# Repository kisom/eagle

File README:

Various EagleCAD projects.

Unless specified otherwise in the schematic frame, all projects are
released under the CC-BY-SA 3.0 license.

Links:
	SFE Eagle parts library: https://github.com/sparkfun/SparkFun-Eagle-Libraries.git
	CC-BY-SA 3.0: http://creativecommons.org/licenses/by-sa/3.0

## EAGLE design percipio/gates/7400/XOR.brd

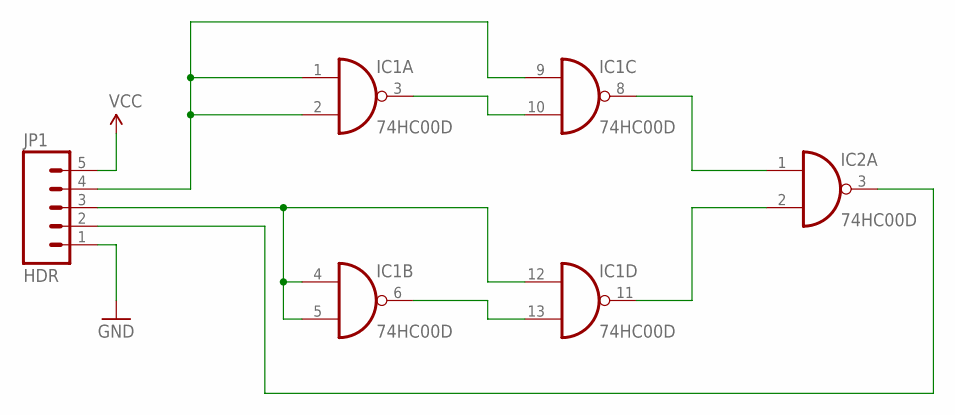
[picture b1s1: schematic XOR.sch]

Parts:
IC1, IC2: 74HC00D; SO14
JP1: HDR; 1X05_LOCK

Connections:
GND: IC1.7 (GND), IC2.7 (GND), JP1.1
unnamed: IC1.1 (I0), IC1.2 (I1), IC1.9 (I0), JP1.4
unnamed: IC1.3 (O), IC1.10 (I1)
unnamed: IC1.6 (O), IC1.13 (I1)
unnamed: IC1.4 (I0), IC1.5 (I1), IC1.12 (I0), JP1.3
unnamed: IC1.8 (O), IC2.1 (I0)
unnamed: IC1.11 (O), IC2.2 (I1)
unnamed: IC2.3 (O), JP1.2
VCC: IC1.14 (VCC), IC2.14 (VCC), JP1.5

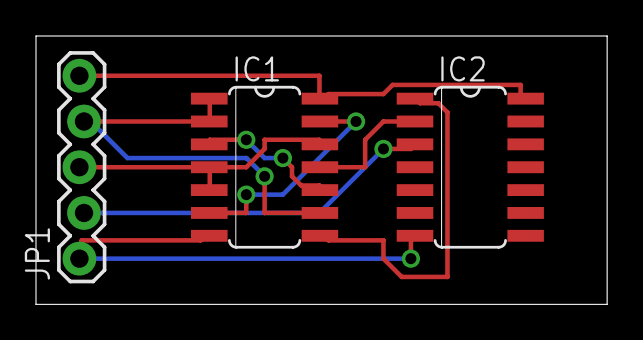
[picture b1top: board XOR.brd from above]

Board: 2 copper layers, 31.7 x 14.9 mm, 3 parts (0 on the bottom side), 9 nets.

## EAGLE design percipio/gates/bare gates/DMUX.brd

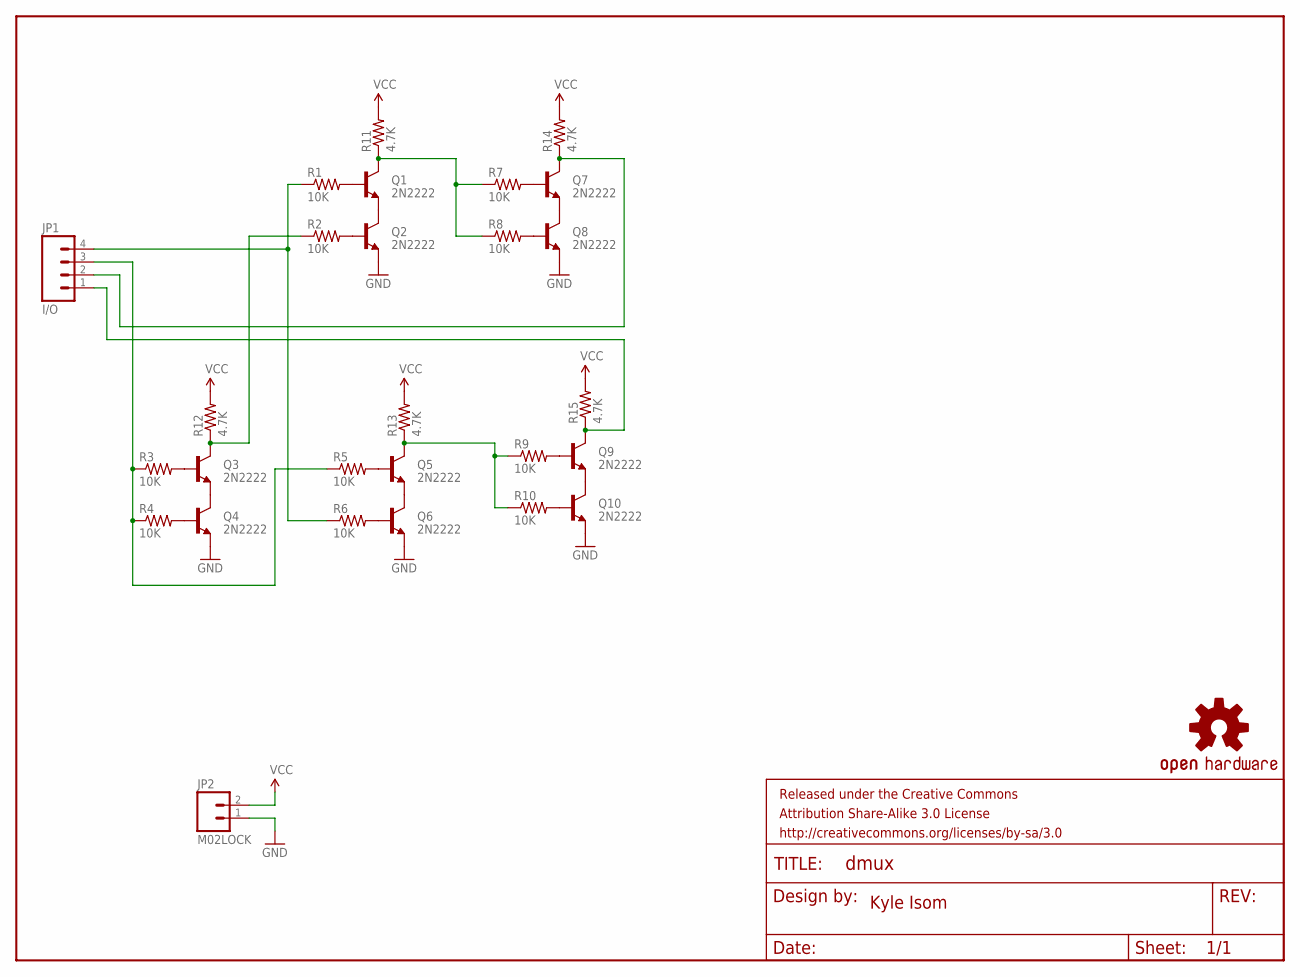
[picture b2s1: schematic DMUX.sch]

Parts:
FRAME1: FRAME-LETTER; CREATIVE_COMMONS
JP1: I/O; 1X04_LOCK
JP2: M02LOCK; 1X02_LOCK
LOGO1: OSHW-LOGOS; OSHW-LOGO-S
Q1, Q2, Q3, Q4, Q5, Q6, Q7, Q8, Q9, Q10: 2N2222; TO-92-AMMO
R1, R2, R3, R4, R5, R6, R7, R8, R9, R10: 10K; AXIAL-0.4
R11, R12, R13, R14, R15: 4.7K; AXIAL-0.4

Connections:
GND: JP2.1, Q2.1 (E), Q4.1 (E), Q6.1 (E), Q8.1 (E), Q10.1 (E)
unnamed: Q1.1 (E), Q2.3 (C)
unnamed: Q3.1 (E), Q4.3 (C)
unnamed: Q5.1 (E), Q6.3 (C)
unnamed: Q7.1 (E), Q8.3 (C)
unnamed: Q9.1 (E), Q10.3 (C)
unnamed: Q1.2 (B), R1.P$2 (2)
unnamed: Q2.2 (B), R2.P$2 (2)
unnamed: Q3.2 (B), R3.P$2 (2)
unnamed: Q4.2 (B), R4.P$2 (2)
unnamed: Q5.2 (B), R5.P$2 (2)
unnamed: Q6.2 (B), R6.P$2 (2)
unnamed: Q8.2 (B), R8.P$2 (2)
unnamed: Q9.2 (B), R9.P$2 (2)
unnamed: Q10.2 (B), R10.P$2 (2)
unnamed: Q7.2 (B), R7.P$2 (2)
unnamed: Q1.3 (C), R7.P$1 (1), R8.P$1 (1), R11.P$1 (1)
unnamed: Q3.3 (C), R2.P$1 (1), R12.P$1 (1)
unnamed: JP1.2, Q7.3 (C), R14.P$1 (1)
unnamed: JP1.1, Q9.3 (C), R15.P$1 (1)
unnamed: JP1.4, R1.P$1 (1), R6.P$1 (1)
unnamed: Q5.3 (C), R9.P$1 (1), R10.P$1 (1), R13.P$1 (1)
unnamed: JP1.3, R3.P$1 (1), R4.P$1 (1), R5.P$1 (1)
VCC: JP2.2, R11.P$2 (2), R12.P$2 (2), R13.P$2 (2), R14.P$2 (2), R15.P$2 (2)

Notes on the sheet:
Kyle Isom

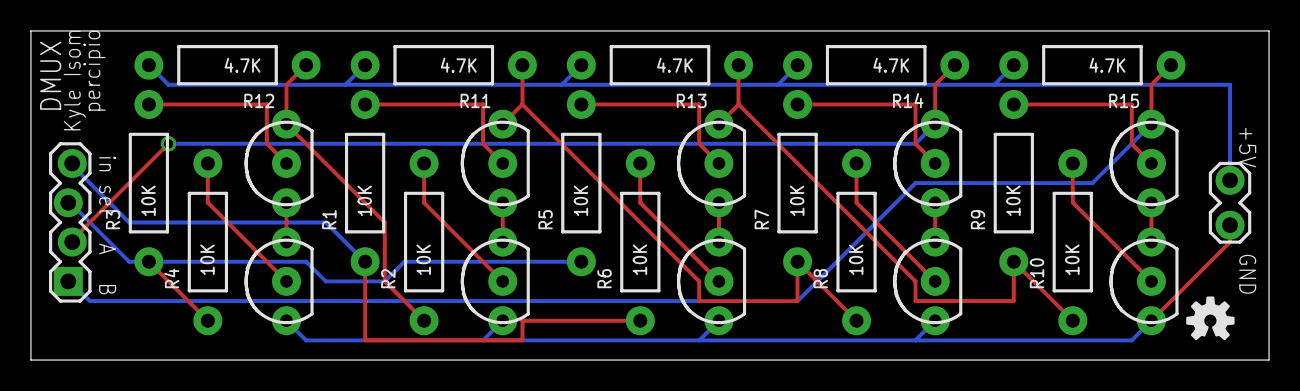
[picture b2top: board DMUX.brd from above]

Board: 2 copper layers, 80.0 x 21.3 mm, 29 parts (0 on the bottom side), 24 nets.

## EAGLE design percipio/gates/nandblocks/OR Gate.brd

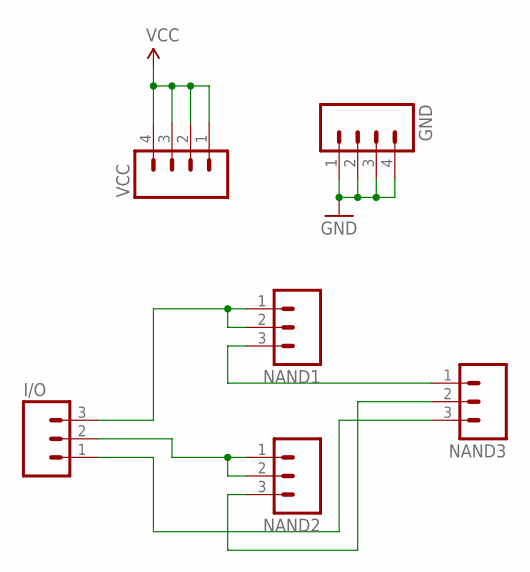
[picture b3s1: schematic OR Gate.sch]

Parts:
GND: M04LOCK; 1X04_LOCK
I/O: M03LOCK; 1X03_LOCK
NAND1, NAND2, NAND3: M03LOCK; 1X03_LOCK
VCC: M04LOCK; 1X04_LOCK

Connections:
GND: GND.1, GND.2, GND.3, GND.4
unnamed: I/O.3, NAND1.1, NAND1.2
unnamed: NAND1.3, NAND3.1
unnamed: I/O.1, NAND3.3
unnamed: I/O.2, NAND2.1, NAND2.2
unnamed: NAND2.3, NAND3.2
VCC: VCC.1, VCC.2, VCC.3, VCC.4

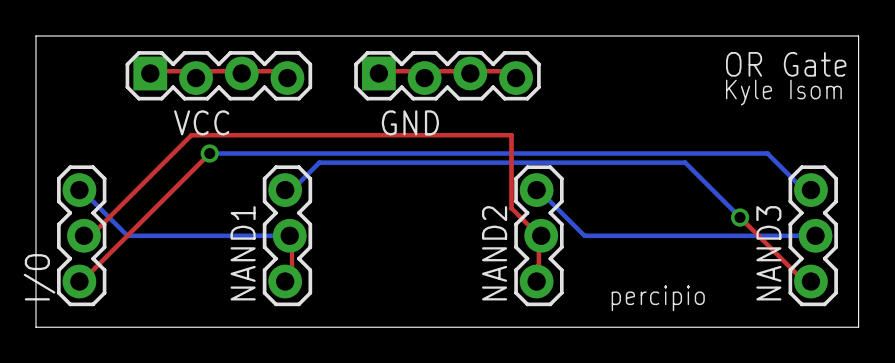
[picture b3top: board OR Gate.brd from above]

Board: 2 copper layers, 45.7 x 16.2 mm, 6 parts (0 on the bottom side), 7 nets.

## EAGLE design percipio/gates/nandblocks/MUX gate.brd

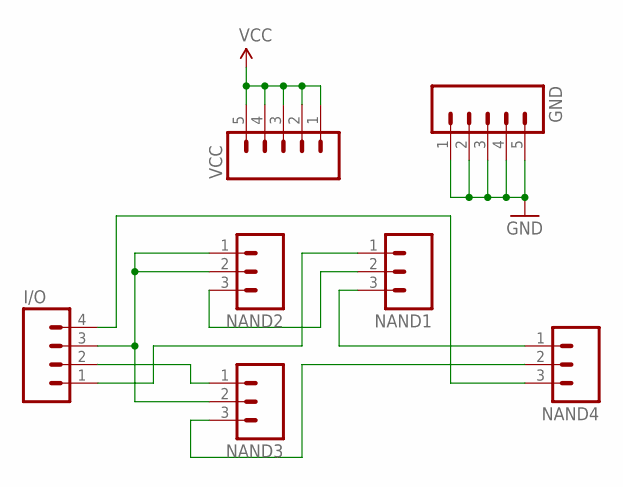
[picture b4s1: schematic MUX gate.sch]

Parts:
GND: M05LOCK; 1X05_LOCK
I/O: M04LOCK; 1X04_LOCK
NAND1, NAND2, NAND3, NAND4: M03LOCK; 1X03_LOCK
VCC: M05LOCK; 1X05_LOCK

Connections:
GND: GND.1, GND.2, GND.3, GND.4, GND.5
unnamed: I/O.1, NAND1.1
unnamed: I/O.2, NAND3.1
unnamed: I/O.3, NAND2.1, NAND2.2, NAND3.2
unnamed: NAND1.2, NAND2.3
unnamed: NAND1.3, NAND4.1
unnamed: NAND3.3, NAND4.2
unnamed: I/O.4, NAND4.3
VCC: VCC.1, VCC.2, VCC.3, VCC.4, VCC.5

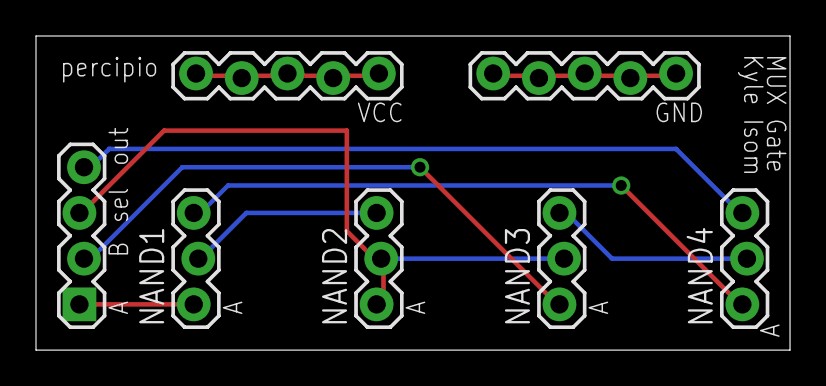
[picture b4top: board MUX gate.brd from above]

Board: 2 copper layers, 41.9 x 17.4 mm, 7 parts (0 on the bottom side), 9 nets.

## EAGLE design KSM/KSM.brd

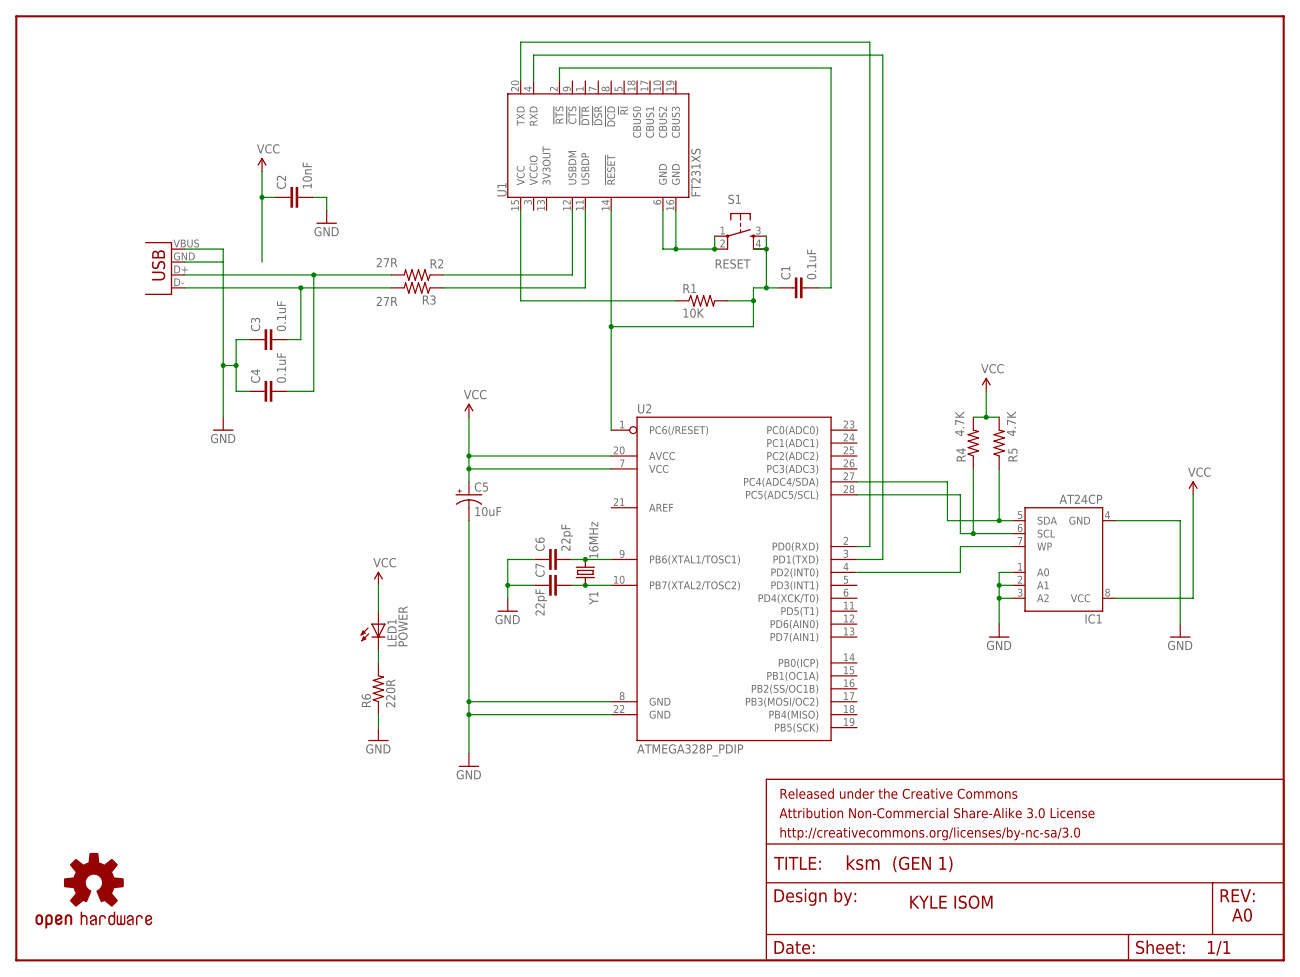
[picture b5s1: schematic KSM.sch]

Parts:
C1, C3, C4: 0.1uF; CAP-PTH-SMALL
C2: 10nF; CAP-PTH-SMALL
C5: 10uF; CPOL-RADIAL-10UF-25V
C6, C7: 22pF; CAP-PTH-SMALL
FRAME1: FRAME-LETTER; CREATIVE_COMMONS
IC1: AT24CP; DIL08
JP1: USB-A-H
LED1: POWER; LED3MM
LOGO1: OSHW-LOGOL; OSHW-LOGO-L
R1: 10K; AXIAL-0.4
R2, R3: 27R; AXIAL-0.4
R4, R5: 4.7K; AXIAL-0.4
R6: 220R; AXIAL-0.4
S1: RESET; TACTILE-PTH
U1: FT231XS; SSOP20_L
U2: ATMEGA328P_PDIP; DIL28-3
Y1: 16MHz; HC49US

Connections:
GND: C2.2, C3.1, C4.1, C5.2 (-), C6.1, C7.1, IC1.1 (A0), IC1.2 (A1), IC1.3 (A2), IC1.4 (GND), JP1.GND (VBUS), JP1.VBUS (GND), R6.P$1 (1), U2.8 (GND), U2.22 (GND)
unnamed: C6.2, U2.9 (PB6(XTAL1/TOSC1)), Y1.2
unnamed: C7.2, U2.10 (PB7(XTAL2/TOSC2)), Y1.1
unnamed: IC1.7 (WP), U2.4 (PD2(INT0))
unnamed: IC1.6 (SCL), R4.P$1 (1), U2.28 (PC5(ADC5/SCL))
unnamed: IC1.5 (SDA), R5.P$1 (1), U2.27 (PC4(ADC4/SDA))
unnamed: R3.P$1 (1), U1.11 (USBDP)
unnamed: R2.P$1 (1), U1.12 (USBDM)
unnamed: C4.2, JP1.D+ (D-), R2.P$2 (2)
unnamed: C3.2, JP1.D- (D+), R3.P$2 (2)
unnamed: S1.1, S1.2, U1.6 (GND), U1.16 (GND)
unnamed: C1.1, R1.P$2 (2), S1.3, S1.4, U1.14 (!RESET), U2.1 (PC6(/RESET))
unnamed: C1.2, U1.2 (!RTS)
unnamed: R1.P$1 (1), U1.15 (VCC)
unnamed: LED1.K (C), R6.P$2 (2)
unnamed: U1.20 (TXD), U2.2 (PD0(RXD))
unnamed: U1.4 (RXD), U2.3 (PD1(TXD))
VCC: C2.1, C5.1 (+), IC1.8 (VCC), LED1.A, R4.P$2 (2), R5.P$2 (2), U2.7 (VCC), U2.20 (AVCC)

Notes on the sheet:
KYLE ISOM
(GEN 1)

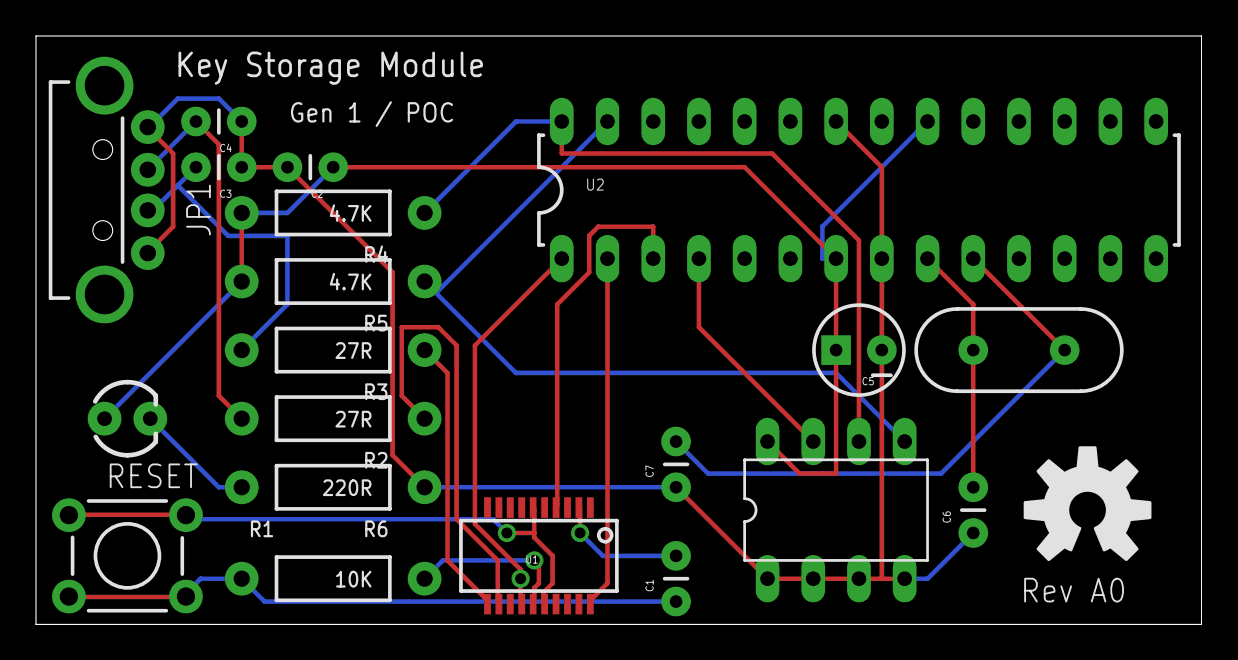
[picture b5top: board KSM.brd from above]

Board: 2 copper layers, 64.8 x 32.7 mm, 22 parts (0 on the bottom side), 18 nets.

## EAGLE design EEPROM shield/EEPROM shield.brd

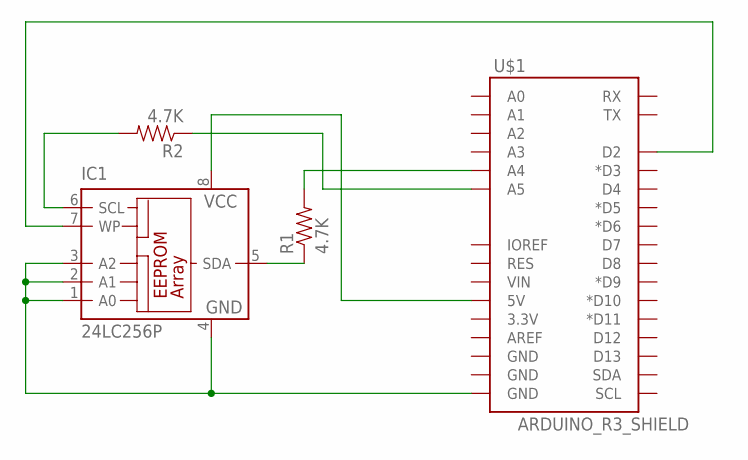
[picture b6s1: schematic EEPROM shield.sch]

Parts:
IC1: 24LC256P; DIL8
R1, R2: 4.7K; AXIAL-0.4
U$1: ARDUINO_R3_SHIELD; UNO_R3_SHIELD

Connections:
unnamed: IC1.7 (WP), U$1.D2
unnamed: IC1.1 (A0), IC1.2 (A1), IC1.3 (A2), IC1.4 (GND), U$1.GND@0 (GND)
unnamed: R1.P$2 (2), U$1.A4
unnamed: R2.P$1 (1), U$1.A5
unnamed: IC1.8 (VCC), U$1.5V
unnamed: IC1.6 (SCL), R2.P$2 (2)
unnamed: IC1.5 (SDA), R1.P$1 (1)

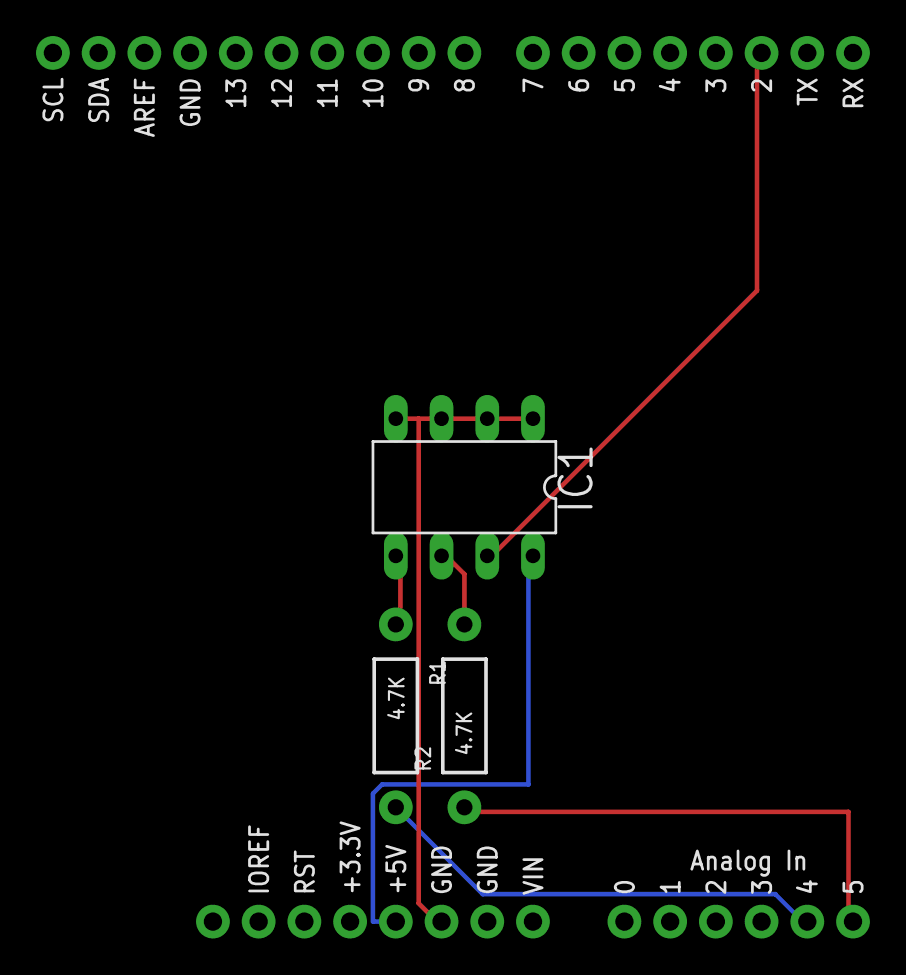
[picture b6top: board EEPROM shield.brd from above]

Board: 2 copper layers, 4 parts (0 on the bottom side), 7 nets.

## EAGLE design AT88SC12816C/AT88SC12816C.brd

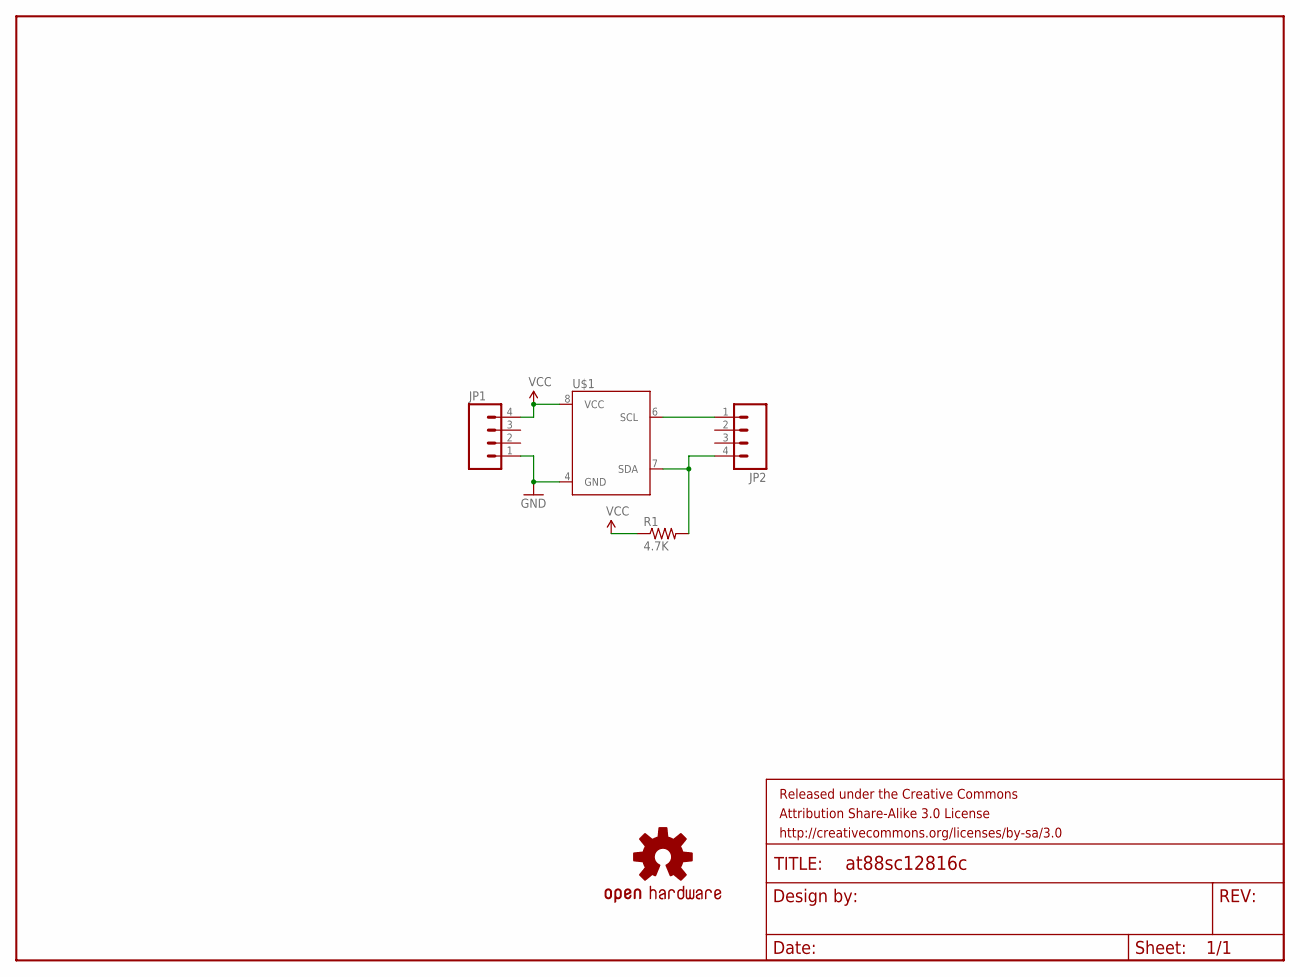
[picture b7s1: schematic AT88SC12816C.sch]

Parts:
FRAME1: FRAME-LETTER; CREATIVE_COMMONS
JP1, JP2: M04LOCK; 1X04_LOCK
LOGO1: OSHW-LOGOM; OSHW-LOGO-M
R1: 4.7K; AXIAL-0.4
U$1: AT88SCAT88SC-PDIP; DIL08

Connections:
GND: JP1.1, U$1.4 (GND)
unnamed: JP2.4, R1.P$2 (2), U$1.7 (SDA)
unnamed: JP2.1, U$1.6 (SCL)
VCC: JP1.4, R1.P$1 (1), U$1.8 (VCC)

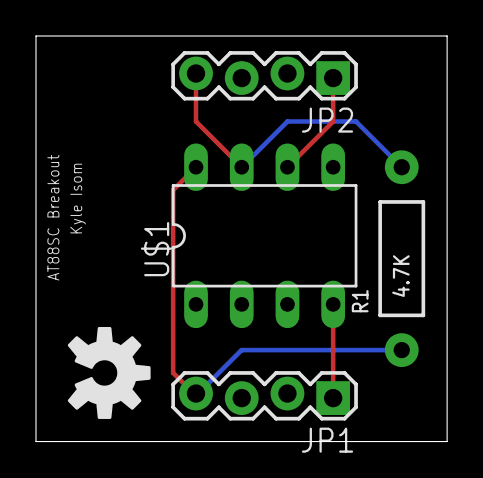
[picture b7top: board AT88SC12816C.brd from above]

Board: 2 copper layers, 22.8 x 22.5 mm, 6 parts (0 on the bottom side), 4 nets.

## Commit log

2014-02-09 initial import
2014-02-09 Add gitignore for the git people.
2014-02-09 Add LICENSE full text (CC-BY-SA 3.0 unported)
2014-02-09 Add README
2014-02-10 Forgot to add .hgignore
2014-02-10 Add DMUX bare board.
2014-02-10 Start 7400 series, renamed XOR gate.

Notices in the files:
parts and their libraries:
SparkFun-Connectors: Licensing: CC v3.0 Share-Alike You are welcome to use this library for commercial purposes.
SparkFun-Aesthetics: Released under the Creative Commons Attribution Share-Alike 3.0 License
SparkFun-Aesthetics: Released under the Creative Commons
